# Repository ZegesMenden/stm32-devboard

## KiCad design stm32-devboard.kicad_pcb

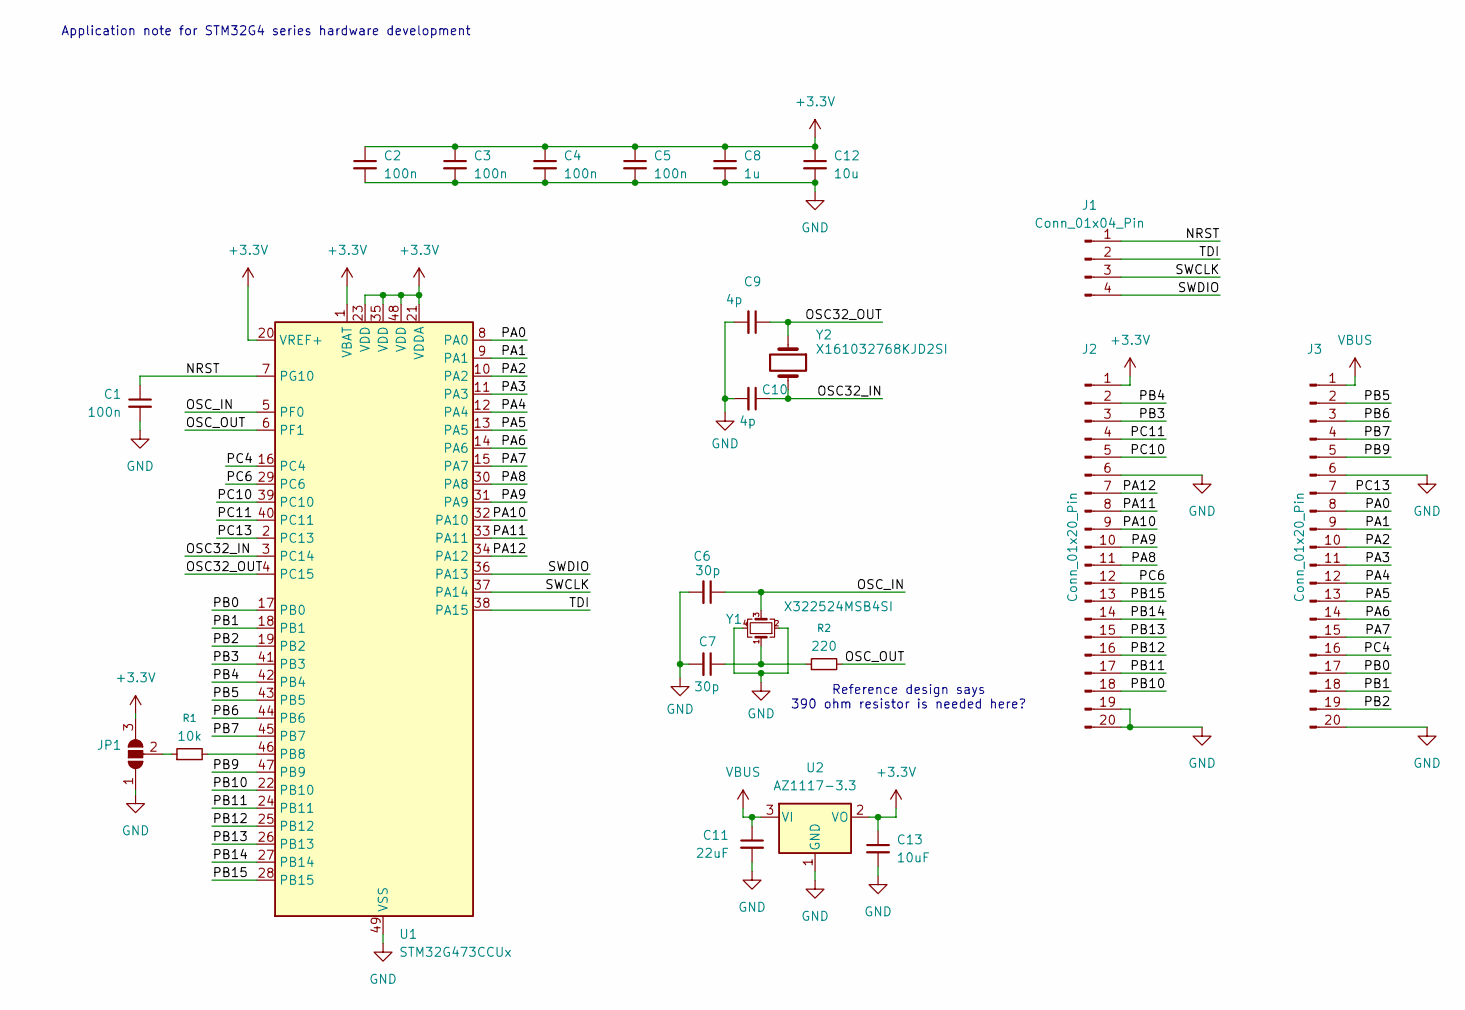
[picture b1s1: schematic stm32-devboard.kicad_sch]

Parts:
C1, C2, C3, C4, C5: 100n; C_0402_1005Metric
C6, C7: 30p; C_0402_1005Metric
C8: 1u; C_0402_1005Metric
C9, C10: 4p; C_0402_1005Metric
C11: 22uF; C_0805_2012Metric
C12: 10u; C_0402_1005Metric
C13: 10uF; C_0402_1005Metric
J1: Conn_01x04_Pin; PinHeader_1x04_P2.54mm_Vertical
J2, J3: Conn_01x20_Pin; PinHeader_1x20_P2.54mm_Vertical
JP1: SolderJumper_3_Open; SolderJumper-3_P1.3mm_Open_RoundedPad1.0x1.5mm
R1: 10k; R_0402_1005Metric
R2: 220; R_0402_1005Metric
U1: STM32G473CCUx; QFN-48-1EP_7x7mm_P0.5mm_EP5.6x5.6mm
U2: AZ1117-3.3; SOT-223-3_TabPin2
Y1: X322524MSB4SI; Crystal_SMD_3225-4Pin_3.2x2.5mm
Y2: X161032768KJD2SI; Crystal_SMD_MicroCrystal_CM9V-T1A-2Pin_1.6x1.0mm

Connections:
+3.3V: C2.1, C3.1, C4.1, C5.1, C8.1, C12.1, C13.1, J2.1, JP1.3 (B), U1.1 (VBAT), U1.20 (VREF+), U1.21 (VDDA), U1.23 (VDD), U1.35 (VDD), U1.48 (VDD), U2.2 (VO)
/NRST: C1.1, J1.1, U1.7 (PG10)
/OSC32_IN: C10.1, U1.3 (PC14), Y2.2
/OSC32_OUT: C9.1, U1.4 (PC15), Y2.1
/OSC_IN: C6.1, U1.5 (PF0), Y1.3
/OSC_OUT: R2.2, U1.6 (PF1)
/PA0: J3.8, U1.8 (PA0)
/PA1: J3.9, U1.9 (PA1)
/PA2: J3.10, U1.10 (PA2)
/PA3: J3.11, U1.11 (PA3)
/PA4: J3.12, U1.12 (PA4)
/PA5: J3.13, U1.13 (PA5)
/PA6: J3.14, U1.14 (PA6)
/PA7: J3.15, U1.15 (PA7)
/PA8: J2.11, U1.30 (PA8)
/PA9: J2.10, U1.31 (PA9)
/PA10: J2.9, U1.32 (PA10)
/PA11: J2.8, U1.33 (PA11)
/PA12: J2.7, U1.34 (PA12)
/PB0: J3.17, U1.17 (PB0)
/PB1: J3.18, U1.18 (PB1)
/PB2: J3.19, U1.19 (PB2)
/PB3: J2.3, U1.41 (PB3)
/PB4: J2.2, U1.42 (PB4)
/PB5: J3.2, U1.43 (PB5)
/PB6: J3.3, U1.44 (PB6)
/PB7: J3.4, U1.45 (PB7)
/PB9: J3.5, U1.47 (PB9)
/PB10: J2.18, U1.22 (PB10)
/PB11: J2.17, U1.24 (PB11)
/PB12: J2.16, U1.25 (PB12)
/PB13: J2.15, U1.26 (PB13)
/PB14: J2.14, U1.27 (PB14)
/PB15: J2.13, U1.28 (PB15)
/PC4: J3.16, U1.16 (PC4)
/PC6: J2.12, U1.29 (PC6)
/PC10: J2.5, U1.39 (PC10)
/PC11: J2.4, U1.40 (PC11)
/PC13: J3.7, U1.2 (PC13)
/SWCLK: J1.3, U1.37 (PA14)
/SWDIO: J1.4, U1.36 (PA13)
/TDI: J1.2, U1.38 (PA15)
GND: C1.2, C2.2, C3.2, C4.2, C5.2, C6.2, C7.2, C8.2, C9.2, C10.2, C11.2, C12.2, C13.2, J2.6, J2.19, J2.20, J3.6, J3.20, JP1.1 (A), U1.49 (VSS), U2.1 (GND), Y1.2, Y1.4
unnamed: C7.1, R2.1, Y1.1
unnamed: JP1.2 (C), R1.1
unnamed: R1.2, U1.46 (PB8)
VBUS: C11.1, J3.1, U2.3 (VI)

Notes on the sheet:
Reference design says 390 ohm resistor is needed here?
Application note for STM32G4 series hardware development

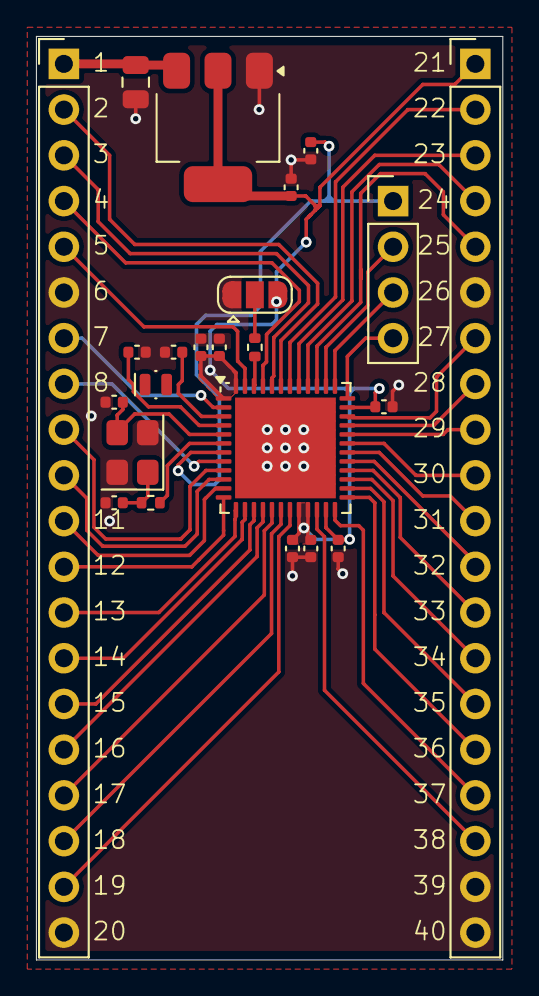
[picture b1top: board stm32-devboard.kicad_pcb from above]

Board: 2 copper layers, 25.9 x 51.3 mm, 23 parts (0 on the bottom side), 47 nets.

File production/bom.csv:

Designator,Footprint,Quantity,Value,LCSC Part #
"C1, C2, C3, C4, C5",0402,5,100n,
"C10, C9",0402,2,4p,
C11,0805,1,22uF,
C12,0402,1,10u,
C13,0402,1,10uF,
"C6, C7",0402,2,30p,
C8,0402,1,1u,
J1,PinHeader_1x04_P2.54mm_Vertical,1,Conn_01x04_Pin,
"J2, J3",PinHeader_1x20_P2.54mm_Vertical,2,Conn_01x20_Pin,
R1,0402,1,10k,
R2,0402,1,220,
U1,QFN-48-1EP_7x7mm_P0.5mm_EP5.6x5.6mm,1,STM32G473CCUx,
U2,SOT-223-3_TabPin2,1,AZ1117-3.3,
Y1,Crystal_SMD_3225-4Pin_3.2x2.5mm,1,X322524MSB4SI,
Y2,Crystal_SMD_MicroCrystal_CM9V-T1A-2Pin_1.6x1.0mm,1,X161032768KJD2SI,

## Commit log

2025-12-01 finished preliminary design
2025-12-02 final revision
2025-12-02 add production files
